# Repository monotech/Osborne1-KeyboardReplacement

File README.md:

# Osborne1-KeyboardReplacement
Replacement keyboard using Cherry MX switches, for if your Osborne 1 keyboard had a bad membrane like mine.

I think there are some Osborne 1 keyboards that are a different layout, which this may not work with.

If your Osborne 1 is like mine, I need an ISO '3' number-row key with £ sign instead of #. I think this comes down to the ROM in your system.

This is a slightly advanced project to mount to the original enclosure. You must:
- Shorten the original 8-32 hex spacers to about half, or buy the replacements in the BoM.
- Shorten the original 8-32 bolts to about 4.5mm thread length, or buy replacements.
- Figure out how to stop the PCB flexing in the middle. Two holes on the PCB are provided to add additional spacers and bolts for the easiest method (drill 2 holes in the original metal faceplate for this). If you wish to not deface the original plate, you will need to fashion something to sit behind the keyboard PCB in the enclosure.

BoM:
- PCB
- 69 x Cherry-MX-compatible keycaps
- 68 x Cherry MX-compatible PCB-mount switches (Cherry MX1A-11NW)
- 1 x Cherry MX Lock switch (Cherry MX1A-31NW)
- 1 x Cherry MX stabiliser kit for 2u-2.75u (Cherry G99-0742)
- 1 x Cherry MX stabiliser kit for 8u-10u (Cherry G99-0744)
- 1 x 2x10-pin 2.54mm vertical locking IDC connector (TE 5499206-4)
- 4 x 3/8" long 8-32 hex spacer (RAF 2102-832-AL)
- 4 x 3/16" threaded-length 8-32 bolts
- 2 x 3/8" long hex spacers (I used M3 threaded) (only used for my method of mounting, involving drilling 2 holes in the front plate)

Notes:
- I recommend Cherry MX Black, as it's closest to the original feel (it feels better imo).
- Cherry MX Lock are obsolete and hard to find. You can replace with another latching switch in a bodgy manner if you can't find one. I found a panel-mount one, and used epoxy for strength since it didn't have the PCB-mounting nubs.
- 9 of the keycaps need to be custom-made, the rest are from standard ANSI and ISO sets. I used the DSA Dolch set from Signature Plastics as my base.

Standard keycaps:
- Letters (26 keys)
- Esc and arrow keys (5 keys)
- Tab (1.5u)
- Numpad 1-9 and . (10 keys)
- Number row, from 1 to = (12 keys) (ANSI or ISO '3' key depending on your ROM)
- Punctuation ( < > ? : " ) (5 keys)
- Backslash/pipe key (1u) (from ISO set)
- Spacebar (8u) (I used their DSA-profile black one)

Custom keycaps:
- Square bracket key (1u)
- Return (2u)
- 2 x Shift (1.5u)
- Alpha Lock (1u)
- Enter (1u)
- Numpad 0 (1u)
- Ctrl (1u)

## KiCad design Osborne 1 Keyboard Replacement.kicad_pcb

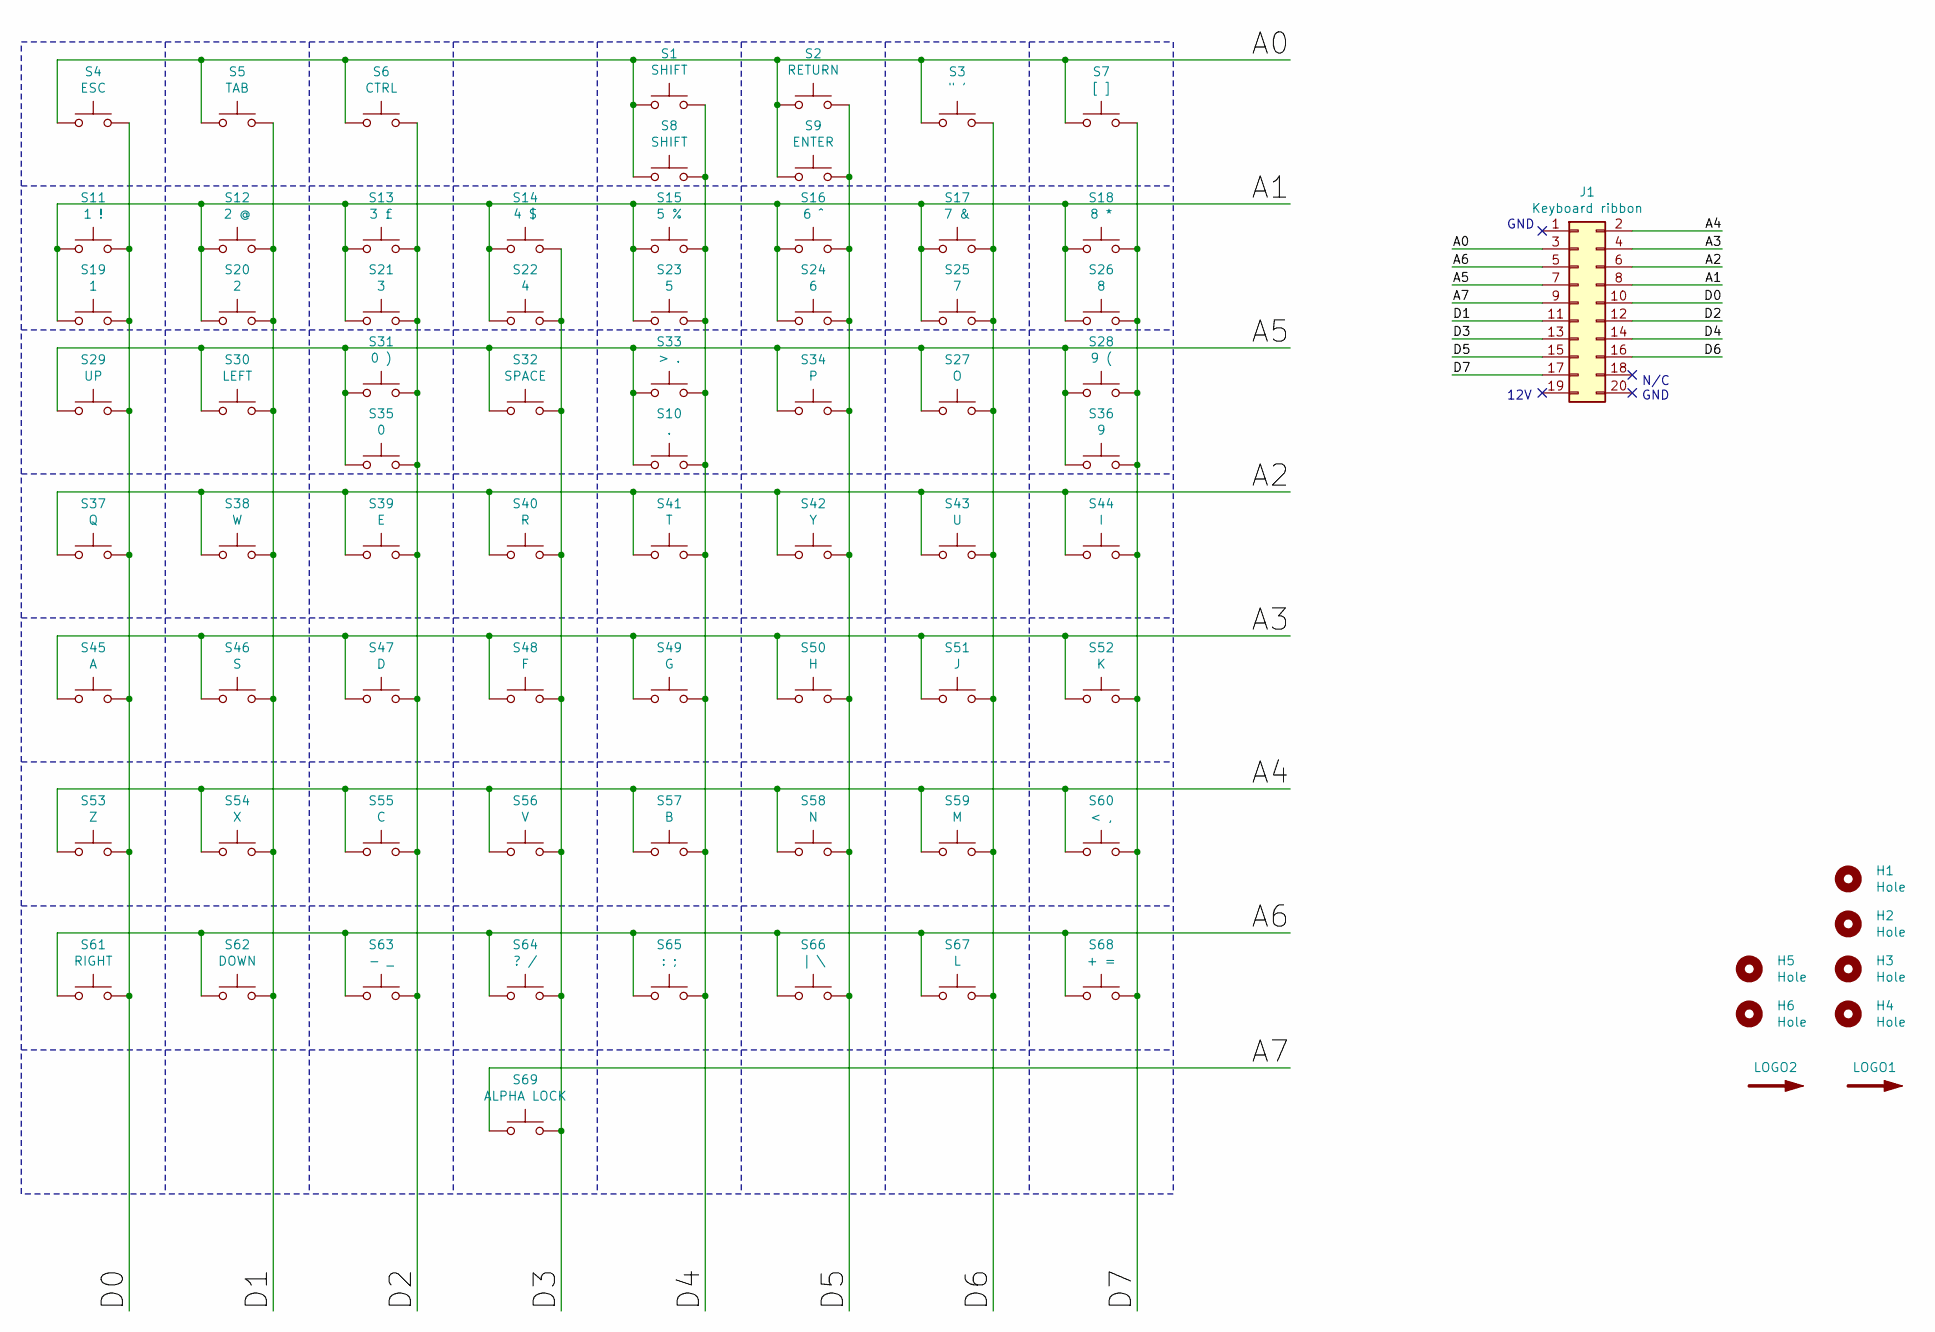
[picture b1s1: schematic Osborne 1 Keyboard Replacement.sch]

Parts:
H1, H2, H3, H4: Hole; MountingHole_4.3mm_M4
H5, H6: Hole; MountingHole_3.2mm_M3
J1: Keyboard ribbon; IDC-Header_2x10_P2.54mm_Vertical_Lock
LOGO1, LOGO2: SYM_Arrow_Large; Monotech Logo 18mm
S1, S8: SHIFT; SW_Cherry_MX_1.50u_PCB
S2: RETURN; SW_Cherry_MX_2.00u_PCB
S3: \" '; SW_Cherry_MX_1.00u_PCB
S4: ESC; SW_Cherry_MX_1.00u_PCB
S5: TAB; SW_Cherry_MX_1.50u_PCB
S6: CTRL; SW_Cherry_MX_1.00u_PCB
S7: [ ]; SW_Cherry_MX_1.00u_PCB
S9: ENTER; SW_Cherry_MX_1.00u_PCB
S10: .; SW_Cherry_MX_1.00u_PCB
S11: 1 !; SW_Cherry_MX_1.00u_PCB
S12: 2 @; SW_Cherry_MX_1.00u_PCB
S13: 3 £; SW_Cherry_MX_1.00u_PCB
S14: 4 $; SW_Cherry_MX_1.00u_PCB
S15: 5 %; SW_Cherry_MX_1.00u_PCB
S16: 6 ^; SW_Cherry_MX_1.00u_PCB
S17: 7 &; SW_Cherry_MX_1.00u_PCB
S18: 8 *; SW_Cherry_MX_1.00u_PCB
S19: 1; SW_Cherry_MX_1.00u_PCB
S20: 2; SW_Cherry_MX_1.00u_PCB
S21: 3; SW_Cherry_MX_1.00u_PCB
S22: 4; SW_Cherry_MX_1.00u_PCB
S23: 5; SW_Cherry_MX_1.00u_PCB
S24: 6; SW_Cherry_MX_1.00u_PCB
S25: 7; SW_Cherry_MX_1.00u_PCB
S26: 8; SW_Cherry_MX_1.00u_PCB
S27: O; SW_Cherry_MX_1.00u_PCB
S28: 9 (; SW_Cherry_MX_1.00u_PCB
S29: UP; SW_Cherry_MX_1.00u_PCB
S30: LEFT; SW_Cherry_MX_1.00u_PCB
S31: 0 ); SW_Cherry_MX_1.00u_PCB
S32: SPACE; SW_Cherry_MX_8u_PCB
S33: > .; SW_Cherry_MX_1.00u_PCB
S34: P; SW_Cherry_MX_1.00u_PCB
S35: 0; SW_Cherry_MX_1.00u_PCB
S36: 9; SW_Cherry_MX_1.00u_PCB
S37: Q; SW_Cherry_MX_1.00u_PCB
S38: W; SW_Cherry_MX_1.00u_PCB
S39: E; SW_Cherry_MX_1.00u_PCB
S40: R; SW_Cherry_MX_1.00u_PCB
S41: T; SW_Cherry_MX_1.00u_PCB
S42: Y; SW_Cherry_MX_1.00u_PCB
S43: U; SW_Cherry_MX_1.00u_PCB
S44: I; SW_Cherry_MX_1.00u_PCB
S45: A; SW_Cherry_MX_1.00u_PCB
S46: S; SW_Cherry_MX_1.00u_PCB
S47: D; SW_Cherry_MX_1.00u_PCB
S48: F; SW_Cherry_MX_1.00u_PCB
S49: G; SW_Cherry_MX_1.00u_PCB
S50: H; SW_Cherry_MX_1.00u_PCB
S51: J; SW_Cherry_MX_1.00u_PCB
S52: K; SW_Cherry_MX_1.00u_PCB
S53: Z; SW_Cherry_MX_1.00u_PCB
S54: X; SW_Cherry_MX_1.00u_PCB
S55: C; SW_Cherry_MX_1.00u_PCB
S56: V; SW_Cherry_MX_1.00u_PCB
S57: B; SW_Cherry_MX_1.00u_PCB
S58: N; SW_Cherry_MX_1.00u_PCB
S59: M; SW_Cherry_MX_1.00u_PCB
S60: < ,; SW_Cherry_MX_1.00u_PCB
S61: RIGHT; SW_Cherry_MX_1.00u_PCB
S62: DOWN; SW_Cherry_MX_1.00u_PCB
S63: - _; SW_Cherry_MX_1.00u_PCB
S64: ? /; SW_Cherry_MX_1.00u_PCB
S65: : ;; SW_Cherry_MX_1.00u_PCB
S66: | \\; SW_Cherry_MX_1.00u_PCB
S67: L; SW_Cherry_MX_1.00u_PCB
S68: + =; SW_Cherry_MX_1.00u_PCB
S69: ALPHA LOCK; SW_Cherry_MX_1.00u_PCB

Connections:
/A0: J1.3, S1.1, S2.1, S3.1, S4.1, S5.1, S6.1, S7.1, S8.1, S9.1
/A1: J1.8, S11.1, S12.1, S13.1, S14.1, S15.1, S16.1, S17.1, S18.1, S19.1, S20.1, S21.1, S22.1, S23.1, S24.1, S25.1, S26.1
/A2: J1.6, S37.1, S38.1, S39.1, S40.1, S41.1, S42.1, S43.1, S44.1
/A3: J1.4, S45.1, S46.1, S47.1, S48.1, S49.1, S50.1, S51.1, S52.1
/A4: J1.2, S53.1, S54.1, S55.1, S56.1, S57.1, S58.1, S59.1, S60.1
/A5: J1.7, S10.1, S27.1, S28.1, S29.1, S30.1, S31.1, S32.1, S33.1, S34.1, S35.1, S36.1
/A6: J1.5, S61.1, S62.1, S63.1, S64.1, S65.1, S66.1, S67.1, S68.1
/A7: J1.9, S69.1
/D0: J1.10, S4.2, S11.2, S19.2, S29.2, S37.2, S45.2, S53.2, S61.2
/D1: J1.11, S5.2, S12.2, S20.2, S30.2, S38.2, S46.2, S54.2, S62.2
/D2: J1.12, S6.2, S13.2, S21.2, S31.2, S35.2, S39.2, S47.2, S55.2, S63.2
/D3: J1.13, S14.2, S22.2, S32.2, S40.2, S48.2, S56.2, S64.2, S69.2
/D4: J1.14, S1.2, S8.2, S10.2, S15.2, S23.2, S33.2, S41.2, S49.2, S57.2, S65.2
/D5: J1.15, S2.2, S9.2, S16.2, S24.2, S34.2, S42.2, S50.2, S58.2, S66.2
/D6: J1.16, S3.2, S17.2, S25.2, S27.2, S43.2, S51.2, S59.2, S67.2
/D7: J1.17, S7.2, S18.2, S26.2, S28.2, S36.2, S44.2, S52.2, S60.2, S68.2

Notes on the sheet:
GND
12V
N/C GND

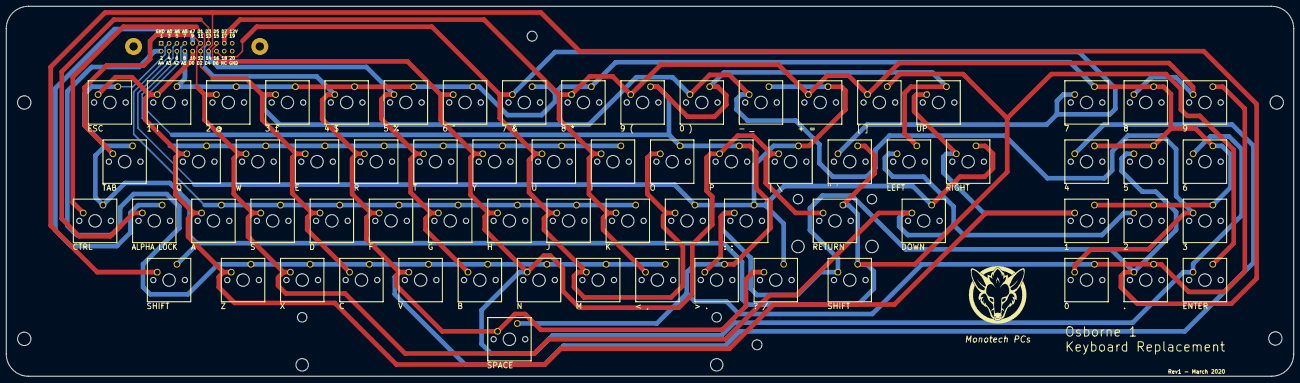
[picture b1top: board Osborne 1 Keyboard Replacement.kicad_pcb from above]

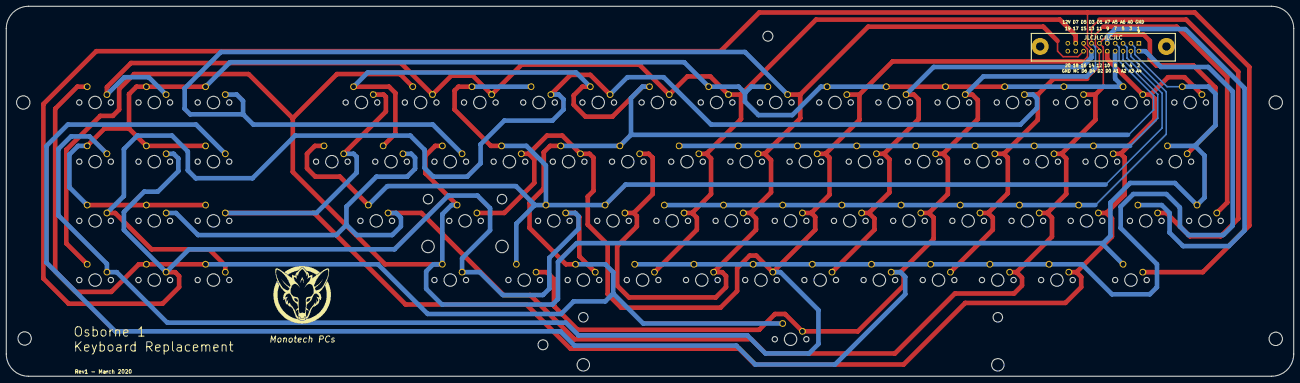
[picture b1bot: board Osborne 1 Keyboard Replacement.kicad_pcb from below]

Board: 2 copper layers, 414.3 x 119.1 mm, 78 parts (2 on the bottom side), 16 nets.
